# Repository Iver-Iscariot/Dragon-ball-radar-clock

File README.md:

# Dragon ball radar watch
A clock based on the dragon-radar from Dragon Ball.<br>
Very basic, pocket watch-style clock, with two rings of 12 LED's (hour/minute).<br>
At the press of the top button, the hour and minute (rounded to closest five) will pulse a couple of times, like in the anime.
&nbsp;

As this will be a novelty item that I only use once in a while, I will forgo a proper RTC, and just rely on the MCU itself for timekeeping. 
To work with the one-button interface of the original, I will set it such that a long-press will set the time to 12 o'clock, so you can simply set it when the actual time is 12 am or pm.<br>

&nbsp;

Progress so far. I need to turn a housing on the lathe

## VERY organized scematic:

## TODO for next PCB itteration:
 - Mosfet poweroff for 4052 multiplexer (power-saving)
 - Perhaps figure out more efficient way of driving the matrix than 4052 (IS31FL3746A LED driver ?)
 - Consider using dedicated RTC, to allow MCU sleep (power saving)
 - Attempt to move LED rings closer to center and make it smaller (LED driver chip would reduce total component footprint)
 - Try out a different LIPO charging circuit (there HAS to be a better way)

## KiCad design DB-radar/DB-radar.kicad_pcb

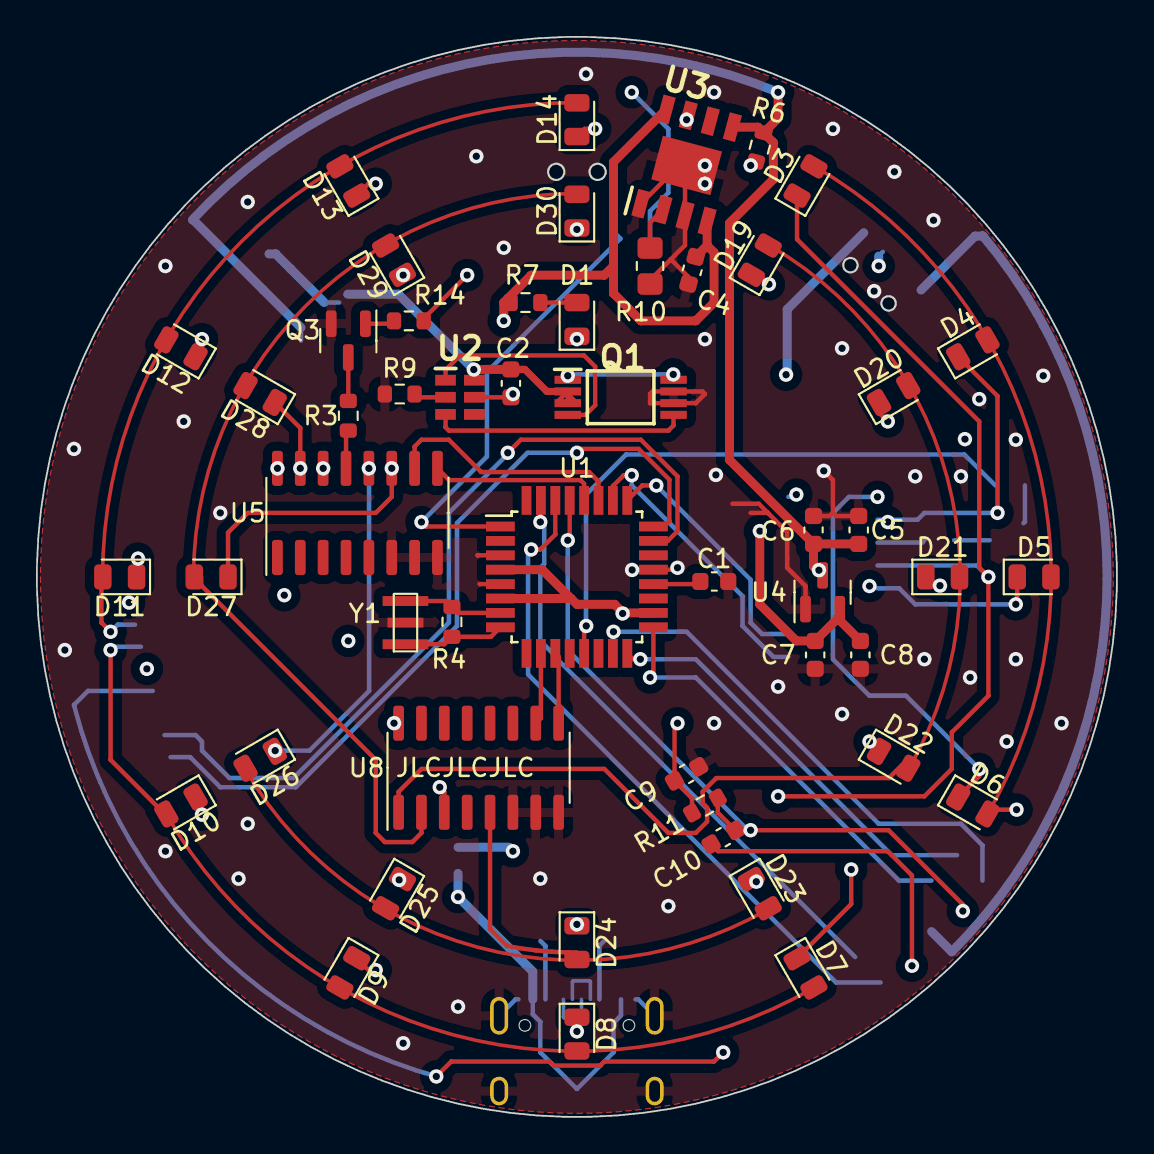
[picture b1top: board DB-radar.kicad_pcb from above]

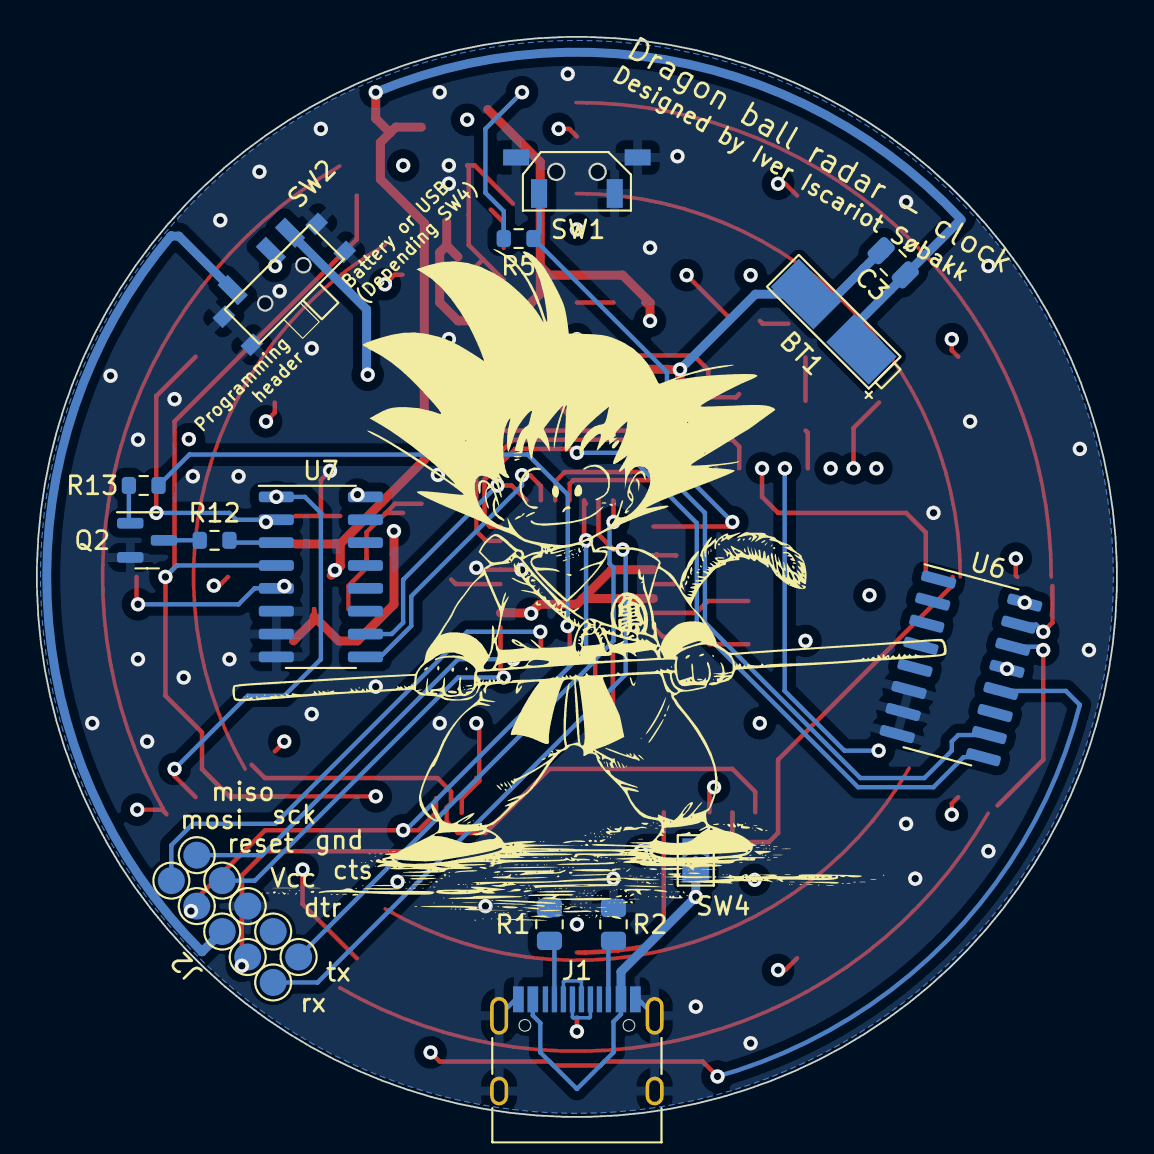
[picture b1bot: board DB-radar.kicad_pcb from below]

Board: 4 copper layers, 60.0 x 60.0 mm, 66 parts (15 on the bottom side), 59 nets.

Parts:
BT1: Battery_Cell; battery pad
C1, C5, C7, C9, C10: 0.1uF; C_0603_1608Metric
C2, C4: 100nF; C_0603_1608Metric
C3: 10uF; C_0805_2012Metric
C6, C8: 1uF; C_0603_1608Metric
D1, D3, D4, D5, D6, D7, D8, D9, D10, D11, D12, D13, D14, D19, D20, D21, D22, D23, D24, D25, D26, D27, D28, D29, D30: LED; LED_0805_2012Metric
J1: USB_C_Receptacle; USB_C_Receptacle_HRO_TYPE-C-31-M-12
J2: Conn_01x10_Female; solder-pad-10-2mm
Q1: FS8205A; SOP65P640X120-8N
Q2, Q3: PN2222A; MMBT2222A
R1, R2: 5.1K; R_0805_2012Metric
R3, R6, R12: 100; R_0603_1608Metric
R4: 1M; R_0603_1608Metric
R5: 2K; R_0603_1608Metric
R7, R9: 1k; R_0603_1608Metric
R10: 1k; R_0805_2012Metric_Pad1.20x1.40mm_HandSolder
R11: 10K; R_0603_1608Metric
R13, R14: 1K; R_0603_1608Metric
SW1: SW_Push; side button
SW2: SW_SPDT; MSK-12C02
SW4: SW_MEC_5G; SolderJumper-2_P1.3mm_Open_TrianglePad1.0x1.5mm
U1: ATmega328PB-A; TQFP-32_7x7mm_P0.8mm
U2: DW01A-G; SOT95P190X145-6N
U3: TP4056; SOIC127P600X175-9N
U4: XC6206PxxxMR; SOT-23
U5, U6, U7, U8: 4052; SOIC-16_3.9x9.9mm_P1.27mm
Y1: Crystal_GND3_Small; 3213 crystal

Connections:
5V: C4.1, J1.A4 (VBUS), J1.A9 (VBUS), J1.B4 (VBUS), J1.B9 (VBUS), R7.1, SW4.1 (A), U3.4 (VCC4), U3.8 (CE)
-BATT: BT1.2 (-), C2.2, C3.2, Q1.2 (S1_1), Q1.3 (S1_2), U2.6 (GND)
A: U1.23 (PC0), U6.10 (A)
B: U1.24 (PC1), U6.9 (B)
BAT+: BT1.1 (+), C3.1, C5.2, C6.2, R6.2, SW4.2 (B), U3.5 (BAT), U4.3 (VI)
BUT_3: R5.2, SW1.2, U1.1 (PD3)
C: U1.25 (PC2), U7.10 (A)
D: U1.26 (PC3), U7.9 (B)
D+: J1.A6 (D+), J1.B6 (D+)
D-: J1.A7 (D-), J1.B7 (D-)
DTR: C10.1, J2.3
E: U1.27 (PC4), U5.10 (A)
F: U1.28 (PC5), U5.9 (B)
G: U1.10 (PD6), U8.10 (A)
GND: C1.1, C4.2, C5.1, C6.1, C7.1, C8.1, C9.2, J1.A1 (GND), J1.A12 (GND), J1.B1 (GND), J1.B12 (GND), J1.S1 (SHIELD), J2.6, Q1.6 (S2_1), Q1.7 (S2_2), Q2.1 (E), Q3.1 (E), R1.1, R2.1, R9.1, R10.1, SW1.1, SW2.S (Shield), U1.3 (PE0), U1.5 (GND), U1.21 (GND), U3.1 (TEMP1), U3.3 (GND_3), U3.9 (EP), U4.1 (GND), U5.6 (Inh), U5.7 (VEE), U5.8 (VSS), U6.6 (Inh), U6.7 (VEE), U6.8 (VSS), U7.6 (Inh), U7.7 (VEE), U7.8 (VSS), U8.6 (Inh), U8.7 (VEE), U8.8 (VSS), Y1.3
H: U1.11 (PD7), U8.9 (B)
LED_PWM: R13.2, R14.2, U1.13 (PB1)
MISO: J2.10, U1.16 (PB4)
MOSI: J2.9, U1.15 (PB3)
unnamed: D1.2 (A), R7.2
unnamed: D1.1 (K), U3.7 (~CHRG)
unnamed: D3.2 (A), D4.2 (A), D5.2 (A), D6.2 (A), U6.12 (X0)
unnamed: D7.2 (A), D8.2 (A), D9.2 (A), D10.2 (A), U6.14 (X1)
unnamed: D6.1 (K), D10.1 (K), D14.1 (K), U7.1 (Y0)
unnamed: D11.2 (A), D12.2 (A), D13.2 (A), D14.2 (A), U6.15 (X2)
unnamed: D3.1 (K), D7.1 (K), D11.1 (K), U7.4 (Y3)
unnamed: D4.1 (K), D8.1 (K), D12.1 (K), U7.2 (Y2)
unnamed: D5.1 (K), D9.1 (K), D13.1 (K), U7.5 (Y1)
unnamed: D19.2 (A), D20.2 (A), D21.2 (A), D22.2 (A), U8.1 (Y0)
unnamed: D19.1 (K), D23.1 (K), D27.1 (K), U5.11 (X3)
unnamed: D20.1 (K), D24.1 (K), D28.1 (K), U5.15 (X2)
unnamed: D21.1 (K), D25.1 (K), D29.1 (K), U5.14 (X1)
unnamed: D22.1 (K), D26.1 (K), D30.1 (K), U5.12 (X0)
unnamed: D23.2 (A), D24.2 (A), D25.2 (A), D26.2 (A), U8.5 (Y1)
unnamed: D27.2 (A), D28.2 (A), D29.2 (A), D30.2 (A), U8.2 (Y2)
unnamed: J1.A5 (CC1), R1.2
unnamed: J1.B5 (CC2), R2.2
unnamed: Q1.1 (D12_1), Q1.8 (D12_2)
unnamed: Q1.4 (G1), U2.1 (OD)
unnamed: Q1.5 (G2), U2.3 (OC)
unnamed: Q2.2 (B), R13.1
unnamed: Q2.3 (C), R12.2
unnamed: Q3.2 (B), R14.1
unnamed: Q3.3 (C), R3.2
unnamed: C1.2, U1.20 (AREF)
unnamed: R4.1, U1.7 (XTAL1/PB6), Y1.2
unnamed: R4.2, U1.8 (XTAL2/PB7), Y1.1
unnamed: R9.2, U2.2 (CS)
unnamed: C2.1, R6.1, U2.5 (VCC)
unnamed: R10.2, U3.2 (PROG2)
unnamed: R3.1, U5.13 (X)
unnamed: R12.1, U7.3 (Y)
RESET: C10.2, J2.7, R11.2, U1.29 (~RESET/PC6)
RX: J2.1, U1.30 (PD0)
SCK: J2.8, U1.17 (PB5)
TX: J2.2, U1.31 (PD1)
VCC: C9.1, R5.1, R11.1, SW2.2 (B), U1.4 (VCC), U1.6 (PE1), U1.18 (AVCC), U5.16 (VDD), U6.13 (X), U6.16 (VDD), U7.16 (VDD), U8.3 (Y), U8.16 (VDD)
VCC_bat: C7.2, C8.2, SW2.1 (A), U4.2 (VO)
VCC_prog: J2.5, SW2.3 (C)

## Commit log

2025-01-03 Made file and started schematic
    Mostly imported from earlier projects.
    Still need to add LED's and multiplexer matrix.
    Note to self: Only need one resistor for minutes and one per hour, as only one will be on at the time
    note: remember to drive LEDs with a PWM pin
2025-01-04 Added LED and multiplexers and started PCB design
2025-01-06 De fleste komponenter plassert
    Mangler bare et par blokker og routing
2025-01-07 Begynnt å route
    Mega-rotete
2025-01-08 Økte til 4 layers og routet ferdig
    Har også kjørt DRC, og det eneste som gjenstår er en GND Zone som den påstår ikke er connected
2025-01-09 Fulførte routing og passed DRC
2025-01-26 Begynnte på et script, men tror jeg fryet chippen somehow
2025-03-13 Se på sketch
2025-03-14 fikset silk bak
    Byttet strøm-selector og SPI kommentarer
2025-03-14 Made a test/demo for the clock
    Rapidly incrementing through the minutes and hours, with no fading
2025-03-14 Oops, small fix
2025-03-15 Working demo
    Last one had wrong lookuptable for outer ring, and minutes and hour switched around
2025-03-15 Begun on actual clock code with button wake-up
2025-03-28 Fake sleep. Hour not working
2025-04-01 3D model for hus
